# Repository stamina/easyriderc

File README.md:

EasyRider
=========

EasyRider REV C is a motorcycle telemetrics project, developed specifically for my Honda C90 classic bike.

The software is written in C using the libopencm3 library for the STM32 446RE Arm Cortex M4 microcontroller.

The PCB's were created with Kicad 6, you'll find all gerbers/schematics/datasheets in the /docs directory.

Functionality
-------------

EasyRider basically does the following things:

- Controls the lighting system: indicators, rear light, brake light, etc.
- Controls the claxon
- Contains an alarm system, based on an IMU
- Reads the motorcycle battery voltage and the power draw of the board
- Contains a buzzer for some startup/alarm sounds
- Reads the RPM of the motor via the CDI, through an opamp and optocoupled circuit
- Logs GPS coordinates and timestamps of events via the external RTC
- Sends all telemetry data over Bluetooth and writes it to onboard Flash.

Overall changes/benefits compared to Rev B
------------------------------------------

- Way more powerful -> Main board: STM32 Nucleo ARM Cortex 4 32bit mcu with Floating Point Unit
- Way easier debugging with SWD (Serial Wire Debug)
- Smaller form-factor size and more modular -> 2 detachable shields -> riser/daughter boards:
  3x stack of 70mmx80mm boards, connected with double 2x19pin headers (76 pins total)
- EasyRelay board: PSU/Relay grid with connectors and 2x 16 port I/O expander IC's
- EasyComm boards: GPS/Bluetooth/IMU/Flash Storage/Sound(buzzer)
   - Adafruit Ultimate GPS Breakout - 66 channel w/10 Hz updates - Version 3
   - Adafruit LSM6DS33 + LIS3MDL - 9 DoF IMU with Accel / Gyro / Mag - STEMMA QT Qwiic
   - Adafruit Bluefruit LE SPI Friend - Bluetooth Low Energy (BLE)
- 4-layer board instead of 2-layer -> less noise, crosstalk
- Lower power -> most IC's at 3.3V, relay coils at 5V
- Lower power -> switching 5V Voltage Regulator instead of Linear
- Radio connectivity: Bluetooth LE low power instead of power-hungry Wifi
- Fast storage for logging/settings/unique ID's/reboots etc. -> 256MBit WinBond SPI flash memory.
- New smaller molex connectors (Mini-Lock)
- More decoupling cap pads at longer traces
- Seperate 12V higher current wire for claxon relay
- Shift registers/IO expander IC before relays/darlington transitor arrays -> less pins needed on Cortex
- Shift registers/IO expander IC before input sense signals -> less pins needed on Cortex

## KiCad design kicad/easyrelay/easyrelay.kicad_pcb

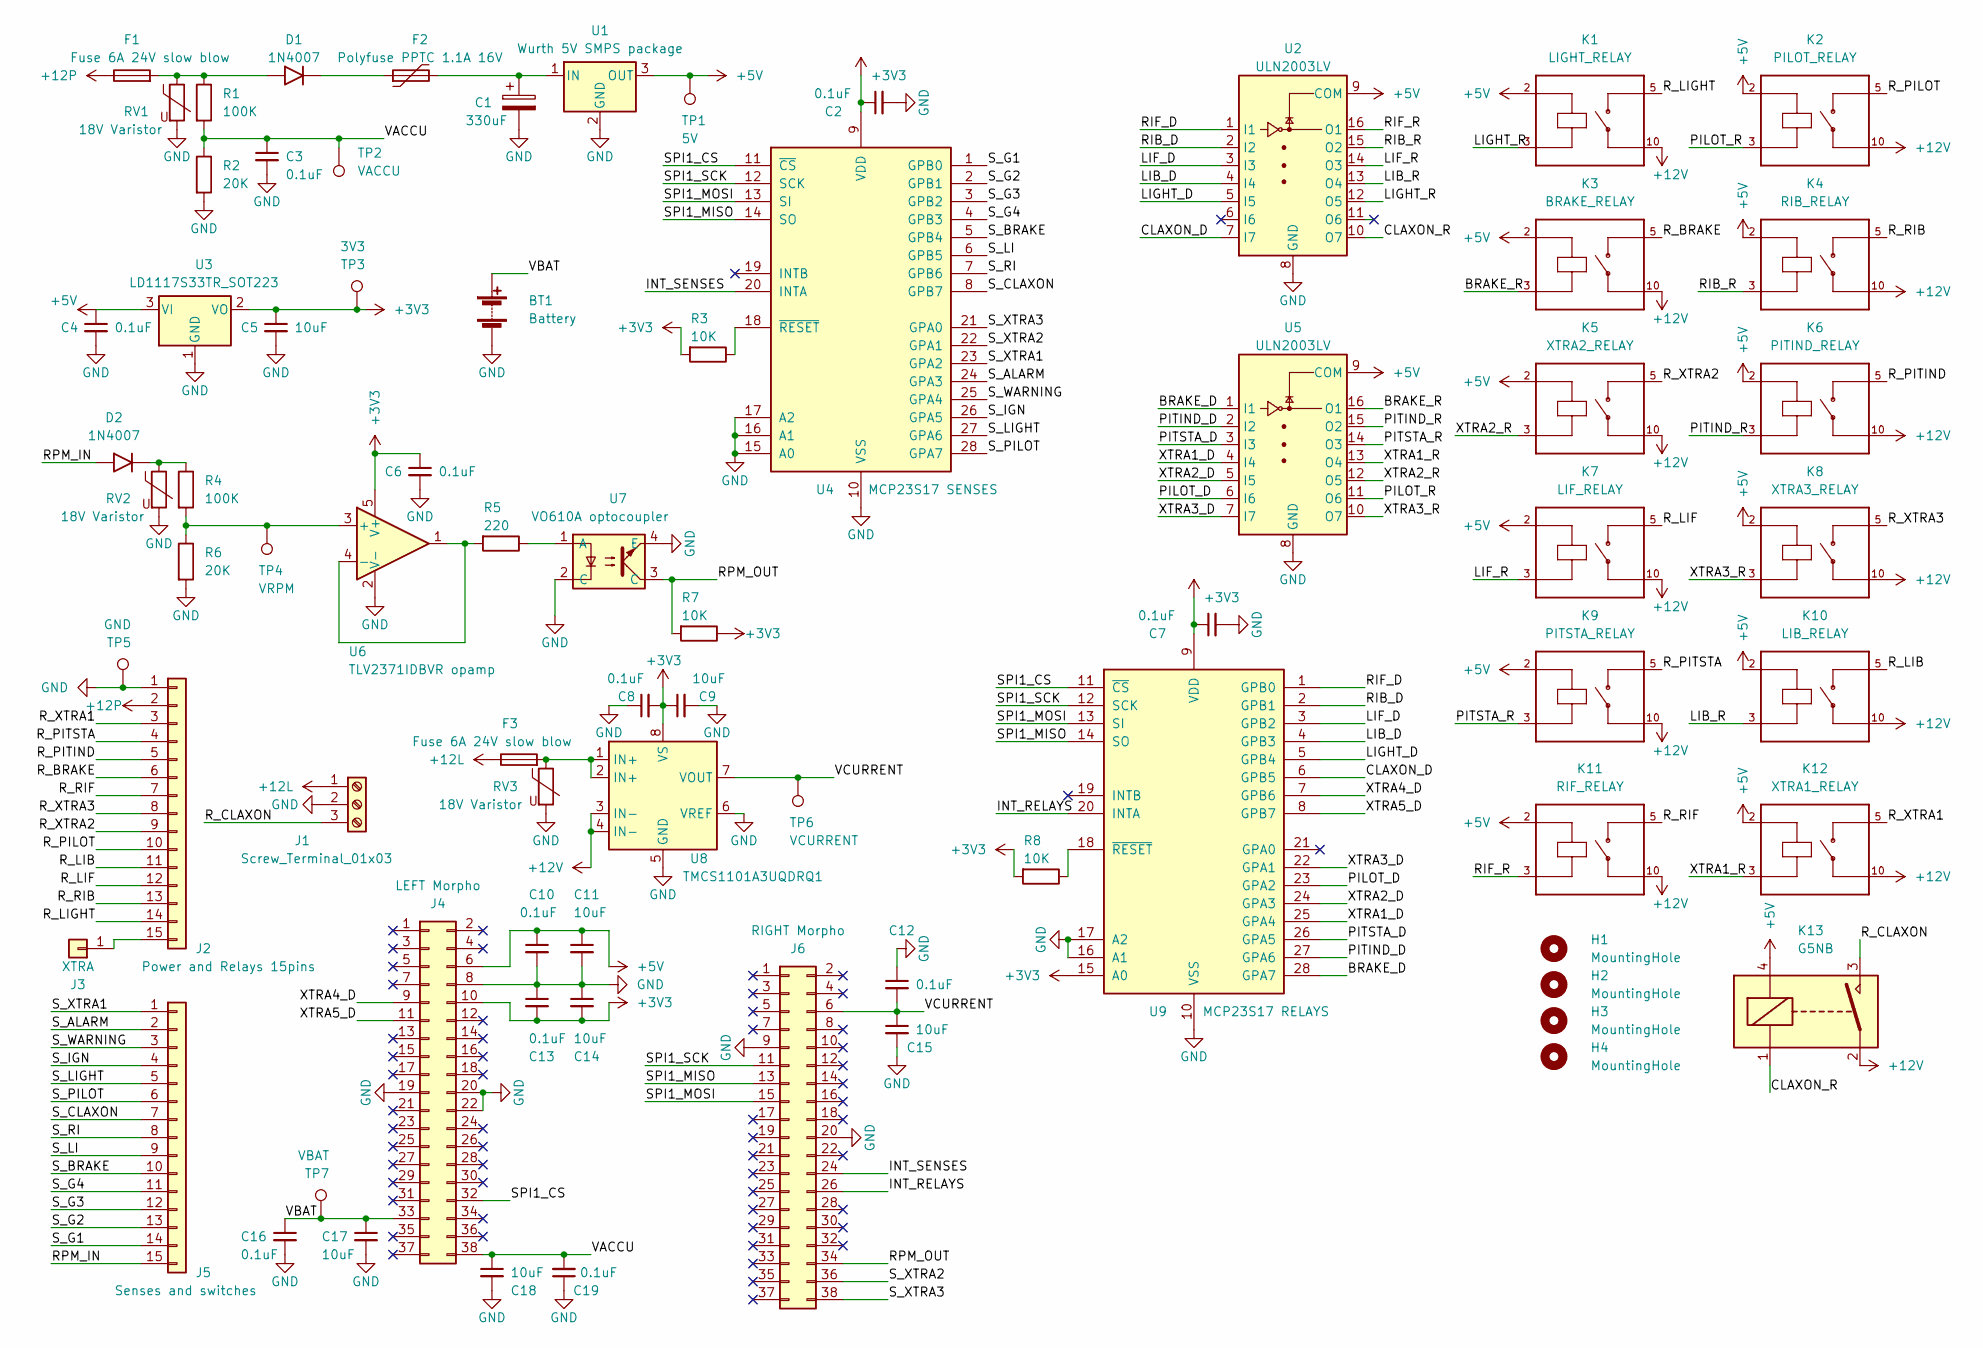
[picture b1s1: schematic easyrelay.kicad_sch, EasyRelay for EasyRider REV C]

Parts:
BT1: Battery; BatteryHolder_Renata SMTU1225-LF
C1: 330uF; CP_Radial_D10.0mm_P5.00mm
C2, C3, C4, C6, C7, C8, C10, C12, C13, C16, C19: 0.1uF; C_0603_1608Metric_Pad1.08x0.95mm_HandSolder
C5, C9, C11, C14, C15, C17, C18: 10uF; C_0603_1608Metric_Pad1.08x0.95mm_HandSolder
D1, D2: 1N4007; D_DO-15_P12.70mm_Horizontal
F1, F3: Fuse 6A 24V slow blow; Fuse_1206_3216Metric
F2: Polyfuse PPTC 1.1A 16V; Fuse_1206_3216Metric
H1, H2, H3, H4: MountingHole; MountingHole_3.2mm_M3
J1: Screw_Terminal_01x03; ScrewTerminalBlock_3_P5.08mm
J2: Power and Relays 15pins; MolexMiniLock_1Ampere_1x15_P2.50mm
J3: XTRA; PinHeader_1x01_P2.54mm_Vertical
J4: LEFT Morpho; PinHeader_2x19_P2.54mm_Vertical
J5: Senses and switches; MolexMiniLock_1Ampere_1x15_P2.50mm
J6: RIGHT Morpho; PinHeader_2x19_P2.54mm_Vertical
K1: LIGHT_RELAY; MEDER RELAY_CRR05-1A
K2: PILOT_RELAY; MEDER RELAY_CRR05-1A
K3: BRAKE_RELAY; MEDER RELAY_CRR05-1A
K4: RIB_RELAY; MEDER RELAY_CRR05-1A
K5: XTRA2_RELAY; MEDER RELAY_CRR05-1A
K6: PITIND_RELAY; MEDER RELAY_CRR05-1A
K7: LIF_RELAY; MEDER RELAY_CRR05-1A
K8: XTRA3_RELAY; MEDER RELAY_CRR05-1A
K9: PITSTA_RELAY; MEDER RELAY_CRR05-1A
K10: LIB_RELAY; MEDER RELAY_CRR05-1A
K11: RIF_RELAY; MEDER RELAY_CRR05-1A
K12: XTRA1_RELAY; MEDER RELAY_CRR05-1A
K13: G5NB; Relay_SPST_Omron-G5NB-1A 5V coil, 12V switch 3Ampere
R1, R4: 100K; R_0603_1608Metric_Pad0.98x0.95mm_HandSolder
R2, R6: 20K; R_0603_1608Metric_Pad0.98x0.95mm_HandSolder
R3, R7, R8: 10K; R_0603_1608Metric_Pad0.98x0.95mm_HandSolder
R5: 220; R_0603_1608Metric_Pad0.98x0.95mm_HandSolder
RV1, RV2, RV3: 18V Varistor; R_0603_1608Metric_Pad0.98x0.95mm_HandSolder
TP1: 5V; PinHeader_1x01_P2.54mm_Vertical
TP2: VACCU; PinHeader_1x01_P2.54mm_Vertical
TP3: 3V3; PinHeader_1x01_P2.54mm_Vertical
TP4: VRPM; PinHeader_1x01_P2.54mm_Vertical
TP5: GND; PinHeader_1x01_P2.54mm_Vertical
TP6: VCURRENT; PinHeader_1x01_P2.54mm_Vertical
TP7: VBAT; PinHeader_1x01_P2.54mm_Vertical
U1: Wurth 5V SMPS package; WURTH-3PIN_FSDM_PACKAGE_TO-220-3_compatible
U2, U5: ULN2003LV; TSSOP16_ULN2003LV
U3: LD1117S33TR_SOT223; SOT-223-3_TabPin2
U4: MCP23S17 SENSES; SSOP-28_5.3x10.2mm_P0.65mm
U6: TLV2371IDBVR opamp; SOT-23-5_HandSoldering
U7: VO610A optocoupler; SMDIP-4_W9.53mm
U8: TMCS1101A3UQDRQ1; SOIC-8_3.9x4.9mm_P1.27mm
U9: MCP23S17 RELAYS; SSOP-28_5.3x10.2mm_P0.65mm

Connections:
+3V3: C2.1, C5.1, C6.1, C7.1, C8.2, C9.1, C13.2, C14.2, J4.10, R3.2, R7.1, R8.2, TP3.1, U3.2 (VO), U4.9 (VDD), U6.5 (V+), U8.8 (VS), U9.9 (VDD), U9.15 (A0); also elsewhere on the board
+5V: C4.1, C10.1, C11.1, J4.6, K1.2, K2.2, K3.2, K4.2, K5.2, K6.2, K7.2, K8.2, K9.2, K10.2, K11.2, K12.2, K13.4, TP1.1, U1.3 (OUT), U2.9 (COM), U3.3 (VI), U5.9 (COM); also elsewhere on the board
+12L: F3.1, J1.1
+12P: F1.1, J2.2
+12V: K1.10, K2.10, K3.10, K4.10, K5.10, K6.10, K7.10, K8.10, K9.10, K10.10, K11.10, K12.10, K13.2, U8.3 (IN-), U8.4 (IN-)
/BRAKE_D: U5.1 (I1), U9.28 (GPA7)
/BRAKE_R: K3.3, U5.16 (O1)
/CLAXON_D: U2.7 (I7), U9.6 (GPB5)
/CLAXON_R: K13.1, U2.10 (O7)
/INT_RELAYS: J6.26, U9.20 (INTA)
/INT_SENSES: J6.24, U4.20 (INTA)
/LIB_D: U2.4 (I4), U9.4 (GPB3)
/LIB_R: K10.3, U2.13 (O4)
/LIF_D: U2.3 (I3), U9.3 (GPB2)
/LIF_R: K7.3, U2.14 (O3)
/LIGHT_D: U2.5 (I5), U9.5 (GPB4)
/LIGHT_R: K1.3, U2.12 (O5)
/PILOT_D: U5.6 (I6), U9.23 (GPA2)
/PILOT_R: K2.3, U5.11 (O6)
/PITIND_D: U5.2 (I2), U9.27 (GPA6)
/PITIND_R: K6.3, U5.15 (O2)
/PITSTA_D: U5.3 (I3), U9.26 (GPA5)
/PITSTA_R: K9.3, U5.14 (O3)
/RIB_D: U2.2 (I2), U9.2 (GPB1)
/RIB_R: K4.3, U2.15 (O2)
/RIF_D: U2.1 (I1), U9.1 (GPB0)
/RIF_R: K11.3, U2.16 (O1)
/RPM_IN: D2.2 (A), J5.15
/RPM_OUT: J6.34, R7.2, U7.3 (C)
/R_BRAKE: J2.6, K3.5
/R_CLAXON: J1.3, K13.3
/R_LIB: J2.11, K10.5
/R_LIF: J2.12, K7.5
/R_LIGHT: J2.14, K1.5
/R_PILOT: J2.10, K2.5
/R_PITIND: J2.5, K6.5
/R_PITSTA: J2.4, K9.5
/R_RIB: J2.13, K4.5
/R_RIF: J2.7, K11.5
/R_XTRA1: J2.3, K12.5
/R_XTRA2: J2.9, K5.5
/R_XTRA3: J2.8, K8.5
/SPI1_CS: J4.32, U4.11 (~CS), U9.11 (~CS)
/SPI1_MISO: J6.13, U4.14 (SO), U9.14 (SO)
/SPI1_MOSI: J6.15, U4.13 (SI), U9.13 (SI)
/SPI1_SCK: J6.11, U4.12 (SCK), U9.12 (SCK)
/S_ALARM: J5.2, U4.24 (GPA3)
/S_BRAKE: J5.10, U4.5 (GPB4)
/S_CLAXON: J5.7, U4.8 (GPB7)
/S_G1: J5.14, U4.1 (GPB0)
/S_G2: J5.13, U4.2 (GPB1)
/S_G3: J5.12, U4.3 (GPB2)
/S_G4: J5.11, U4.4 (GPB3)
/S_IGN: J5.4, U4.26 (GPA5)
/S_LI: J5.9, U4.6 (GPB5)
/S_LIGHT: J5.5, U4.27 (GPA6)
/S_PILOT: J5.6, U4.28 (GPA7)
/S_RI: J5.8, U4.7 (GPB6)
/S_WARNING: J5.3, U4.25 (GPA4)
/S_XTRA1: J5.1, U4.23 (GPA2)
/S_XTRA2: J6.36, U4.22 (GPA1)
/S_XTRA3: J6.38, U4.21 (GPA0)
/VACCU: C3.1, C18.1, C19.2, J4.38, R1.2, R2.1, TP2.1; also elsewhere on the board
/VBAT: BT1.1 (+), C16.1, C17.1, J4.33, TP7.1; also elsewhere on the board
/VCURRENT: C12.2, C15.1, J6.6, TP6.1, U8.7 (VOUT); also elsewhere on the board
/XTRA1_D: U5.4 (I4), U9.25 (GPA4)
/XTRA1_R: K12.3, U5.13 (O4)
/XTRA2_D: U5.5 (I5), U9.24 (GPA3)
/XTRA2_R: K5.3, U5.12 (O5)
/XTRA3_D: U5.7 (I7), U9.22 (GPA1)
/XTRA3_R: K8.3, U5.10 (O7)
/XTRA4_D: J4.9, U9.7 (GPB6)
/XTRA5_D: J4.11, U9.8 (GPB7)
GND: BT1.2 (-), C1.2, C2.2, C3.2, C4.2, C5.2, C6.2, C7.2, C8.1, C9.2, C10.2, C11.2, C12.1, C13.1, C14.1, C15.2, C16.2, C17.2, C18.2, C19.1, J1.2, J2.1, J4.8, J4.19, J4.20, J4.22, J6.9, J6.20, R2.2, R6.2, RV1.2, RV2.2, RV3.2, TP5.1, U1.2 (GND), U2.8 (GND), U3.1 (GND), U4.10 (VSS), U4.15 (A0), U4.16 (A1), U4.17 (A2), U5.8 (GND), U6.2 (V-), U7.2 (C), U7.4 (E), U8.5 (GND), U8.6 (VREF), U9.10 (VSS), U9.16 (A1), U9.17 (A2); also elsewhere on the board
unnamed: C1.1, F2.2, U1.1 (IN)
unnamed: D1.1 (K), F2.1
unnamed: D1.2 (A), F1.2, R1.1, RV1.1
unnamed: D2.1 (K), R4.1, RV2.1
unnamed: F3.2, RV3.1, U8.1 (IN+), U8.2 (IN+)
unnamed: J2.15, J3.1
unnamed: R3.1, U4.18 (~RESET)
unnamed 81: R4.2, R6.1, TP4.1, U6.3 (+); also elsewhere on the board
unnamed: R5.1, U7.1 (A)
unnamed: R5.2, U6.1, U6.4 (-)
unnamed: R8.1, U9.18 (~RESET)

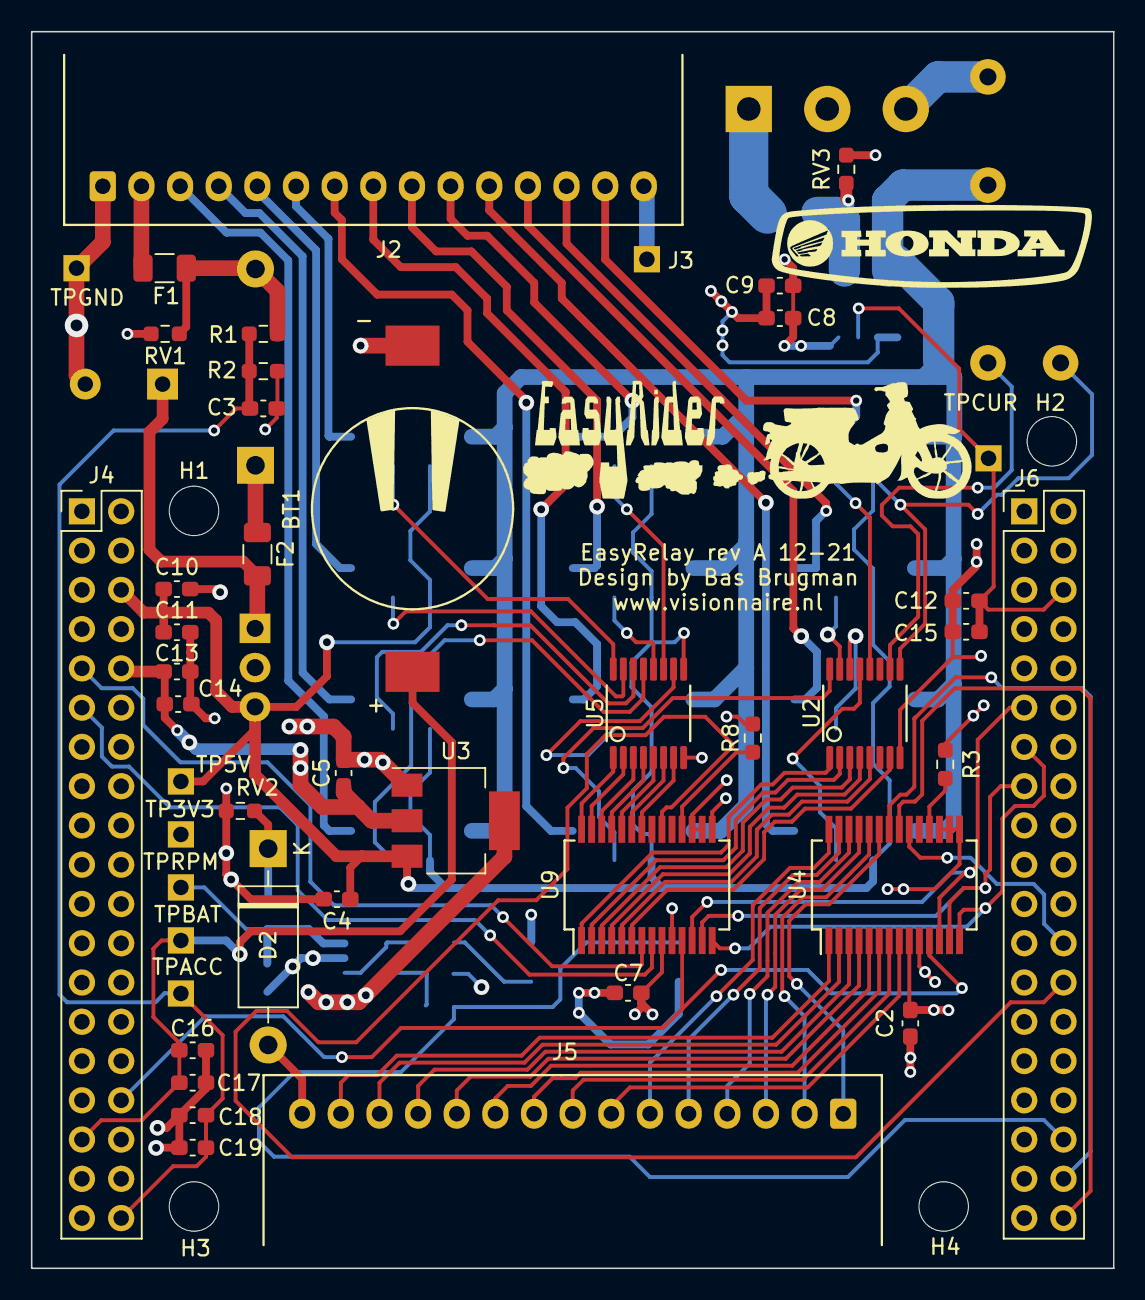
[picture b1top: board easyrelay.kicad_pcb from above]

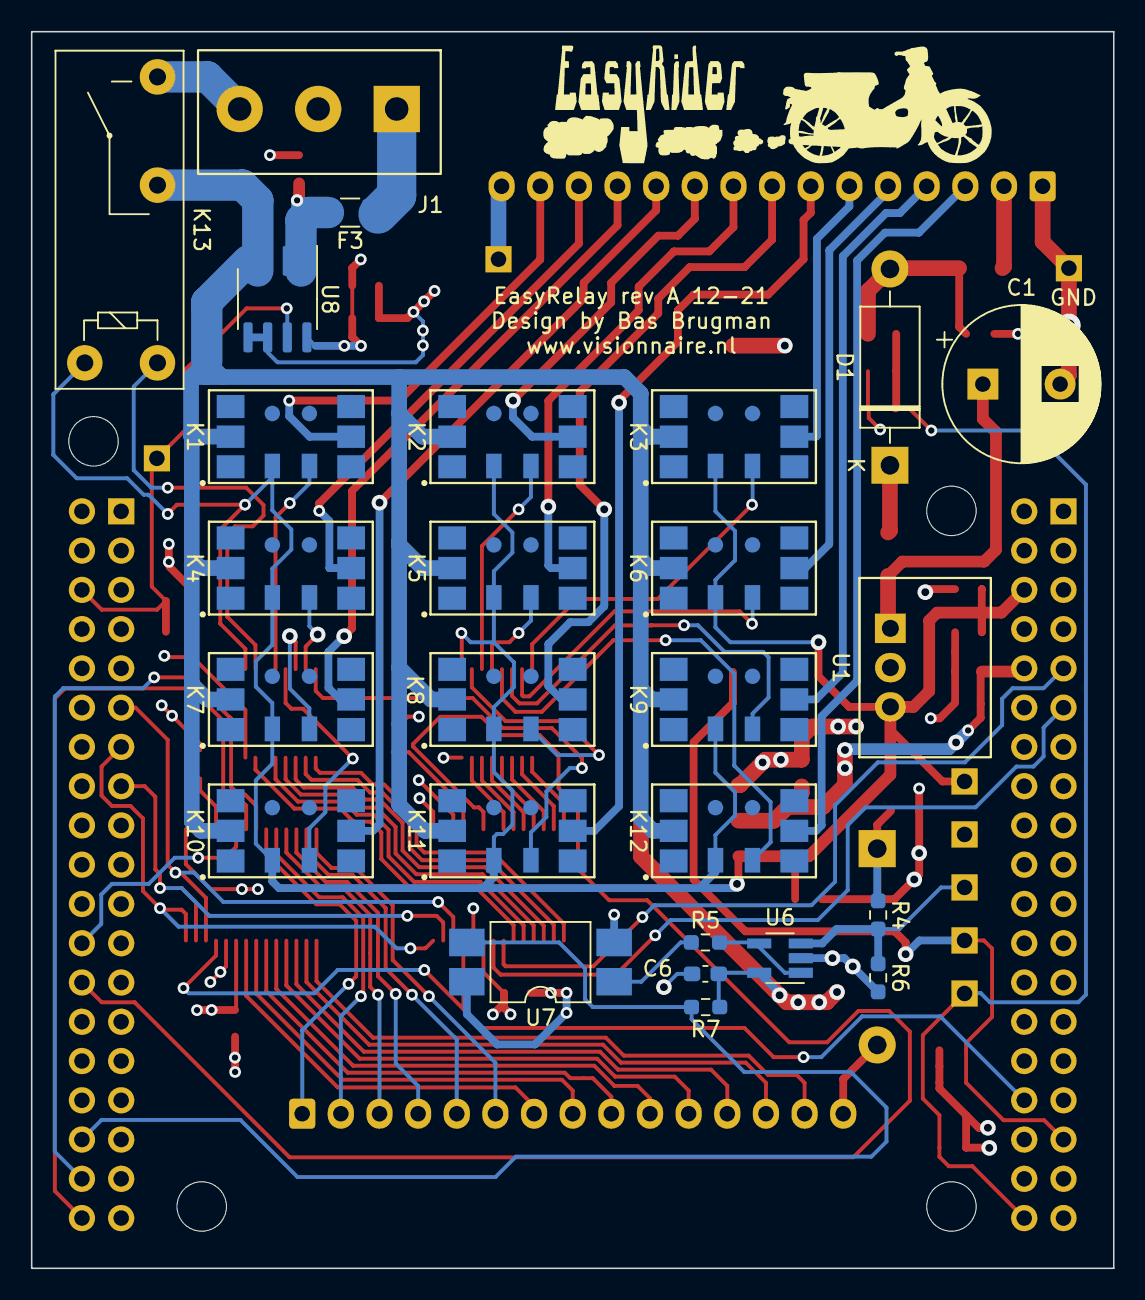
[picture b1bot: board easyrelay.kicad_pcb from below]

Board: 4 copper layers, 70.0 x 80.0 mm, 75 parts (27 on the bottom side), 85 nets.

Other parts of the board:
TP3V3: 3V3; PinHeader_1x01_P2.54mm_Vertical
TP5V: 5V; PinHeader_1x01_P2.54mm_Vertical
TPACC: VACCU; PinHeader_1x01_P2.54mm_Vertical
TPBAT: VBAT; PinHeader_1x01_P2.54mm_Vertical
TPCUR: VCURRENT; PinHeader_1x01_P2.54mm_Vertical
TPGND: GND; PinHeader_1x01_P2.54mm_Vertical
TPRPM: VRPM; PinHeader_1x01_P2.54mm_Vertical

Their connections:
+3V3: TP3V3.1; also elsewhere on the board
+5V: TP5V.1; also elsewhere on the board
/VACCU: TPACC.1; also elsewhere on the board
/VBAT: TPBAT.1; also elsewhere on the board
/VCURRENT: TPCUR.1; also elsewhere on the board
GND: TPGND.1; also elsewhere on the board
unnamed 81: TPRPM.1; also elsewhere on the board

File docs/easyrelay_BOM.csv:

"Id";"Designator";"Package";"Quantity";"Designation";"Supplier and ref";
1;"U2,U5";"TSSOP16_ULN2003LV";2;"ULN2003LV";;;
2;"H4,H3,H2,H1";"MountingHole_3.2mm_M3";4;"MountingHole";;;
3;"J4";"PinHeader_2x19_P2.54mm_Vertical";1;"LEFT Morpho";;;
4;"BT1";"BatteryHolder_Renata SMTU1225-LF";1;"Battery";;;
5;"R2,R6";"R_0603_1608Metric_Pad0.98x0.95mm_HandSolder";2;"20K";;;
6;"C18,C5,C14,C15,C17,C9,C11";"C_0603_1608Metric_Pad1.08x0.95mm_HandSolder";7;"10uF";;;
7;"R8,R3,R7";"R_0603_1608Metric_Pad0.98x0.95mm_HandSolder";3;"10K";;;
8;"C4,C2,C13,C10,C12,C16,C8,C3,C19,C7,C6";"C_0603_1608Metric_Pad1.08x0.95mm_HandSolder";11;"0.1uF";;;
9;"TP5V";"PinHeader_1x01_P2.54mm_Vertical";1;"5V";;;
10;"U9";"SSOP-28_5.3x10.2mm_P0.65mm";1;"MCP23S17 RELAYS";;;
11;"TPCUR";"PinHeader_1x01_P2.54mm_Vertical";1;"VCURRENT";;;
12;"RV2,RV1,RV3";"R_0603_1608Metric_Pad0.98x0.95mm_HandSolder";3;"18V Varistor";;;
13;"U3";"SOT-223-3_TabPin2";1;"LD1117S33TR_SOT223";;;
14;"D2,D1";"D_DO-15_P12.70mm_Horizontal";2;"1N4007";;;
15;"J5";"MolexMiniLock_1Ampere_1x15_P2.50mm";1;"Senses and switches";;;
16;"F1,F3";"Fuse_1206_3216Metric";2;"Fuse 6A 24V slow blow";;;
17;"R1,R4";"R_0603_1608Metric_Pad0.98x0.95mm_HandSolder";2;"100K";;;
18;"TP3V3";"PinHeader_1x01_P2.54mm_Vertical";1;"3V3";;;
19;"TPRPM";"PinHeader_1x01_P2.54mm_Vertical";1;"VRPM";;;
20;"J3";"PinHeader_1x01_P2.54mm_Vertical";1;"XTRA";;;
21;"J6";"PinHeader_2x19_P2.54mm_Vertical";1;"RIGHT Morpho";;;
22;"TPBAT";"PinHeader_1x01_P2.54mm_Vertical";1;"VBAT";;;
23;"U4";"SSOP-28_5.3x10.2mm_P0.65mm";1;"MCP23S17 SENSES";;;
24;"G***,G***";"EasyRider_logo1";2;"LOGO";;;
25;"J2";"MolexMiniLock_1Ampere_1x15_P2.50mm";1;"Power and Relays 15pins";;;
26;"TPACC";"PinHeader_1x01_P2.54mm_Vertical";1;"VACCU";;;
27;"F2";"Fuse_1206_3216Metric";1;"Polyfuse PPTC 1.1A 16V";;;
28;"G***";"EasyRider_logo2";1;"LOGO";;;
29;"K1";"MEDER RELAY_CRR05-1A";1;"LIGHT_RELAY";;;
30;"U7";"SMDIP-4_W9.53mm";1;"VO610A optocoupler";;;
31;"K11";"MEDER RELAY_CRR05-1A";1;"RIF_RELAY";;;
32;"K4";"MEDER RELAY_CRR05-1A";1;"RIB_RELAY";;;
33;"K6";"MEDER RELAY_CRR05-1A";1;"PITIND_RELAY";;;
34;"U8";"SOIC-8_3.9x4.9mm_P1.27mm";1;"TMCS1101A3UQDRQ1";;;
35;"J1";"ScrewTerminalBlock_3_P5.08mm";1;"Screw_Terminal_01x03";;;
36;"K8";"MEDER RELAY_CRR05-1A";1;"XTRA3_RELAY";;;
37;"K9";"MEDER RELAY_CRR05-1A";1;"PITSTA_RELAY";;;
38;"K2";"MEDER RELAY_CRR05-1A";1;"PILOT_RELAY";;;
39;"K12";"MEDER RELAY_CRR05-1A";1;"XTRA1_RELAY";;;
40;"K10";"MEDER RELAY_CRR05-1A";1;"LIB_RELAY";;;
41;"K13";"Relay_SPST_Omron-G5NB-1A 5V coil, 12V switch 3Ampere";1;"G5NB";;;
42;"C1";"CP_Radial_D10.0mm_P5.00mm";1;"330uF";;;
43;"K3";"MEDER RELAY_CRR05-1A";1;"BRAKE_RELAY";;;
44;"U1";"WURTH-3PIN_FSDM_PACKAGE_TO-220-3_compatible";1;"Wurth 5V SMPS package";;;
45;"K5";"MEDER RELAY_CRR05-1A";1;"XTRA2_RELAY";;;
46;"TPGND";"PinHeader_1x01_P2.54mm_Vertical";1;"GND";;;
47;"R5";"R_0603_1608Metric_Pad0.98x0.95mm_HandSolder";1;"220";;;
48;"K7";"MEDER RELAY_CRR05-1A";1;"LIF_RELAY";;;
49;"U6";"SOT-23-5_HandSoldering";1;"TLV2371IDBVR opamp";;;

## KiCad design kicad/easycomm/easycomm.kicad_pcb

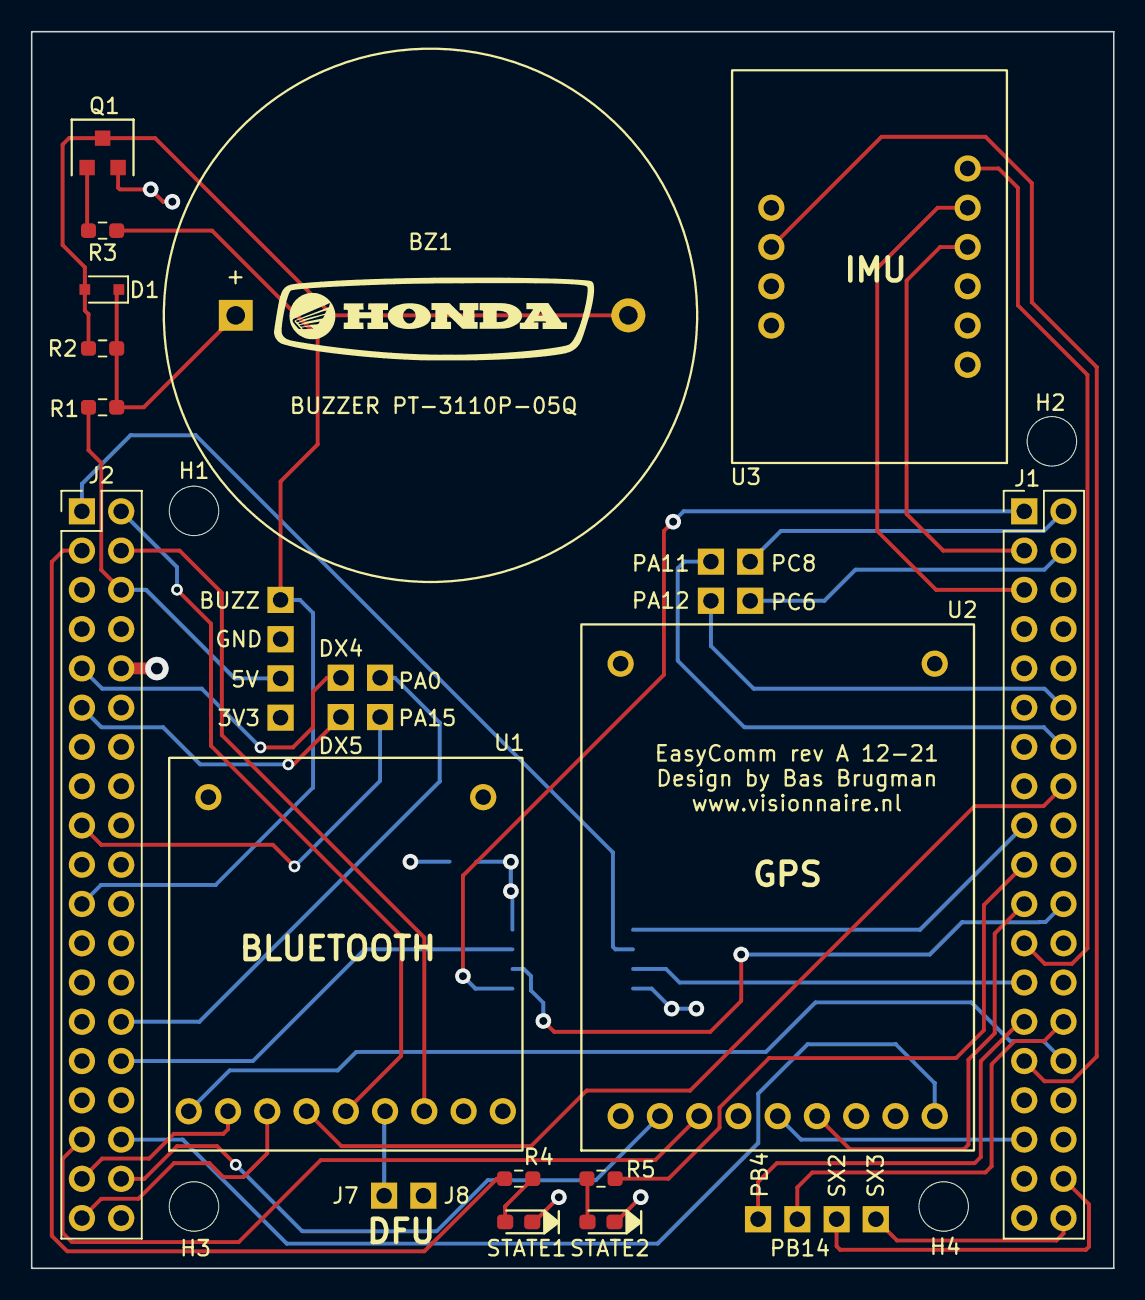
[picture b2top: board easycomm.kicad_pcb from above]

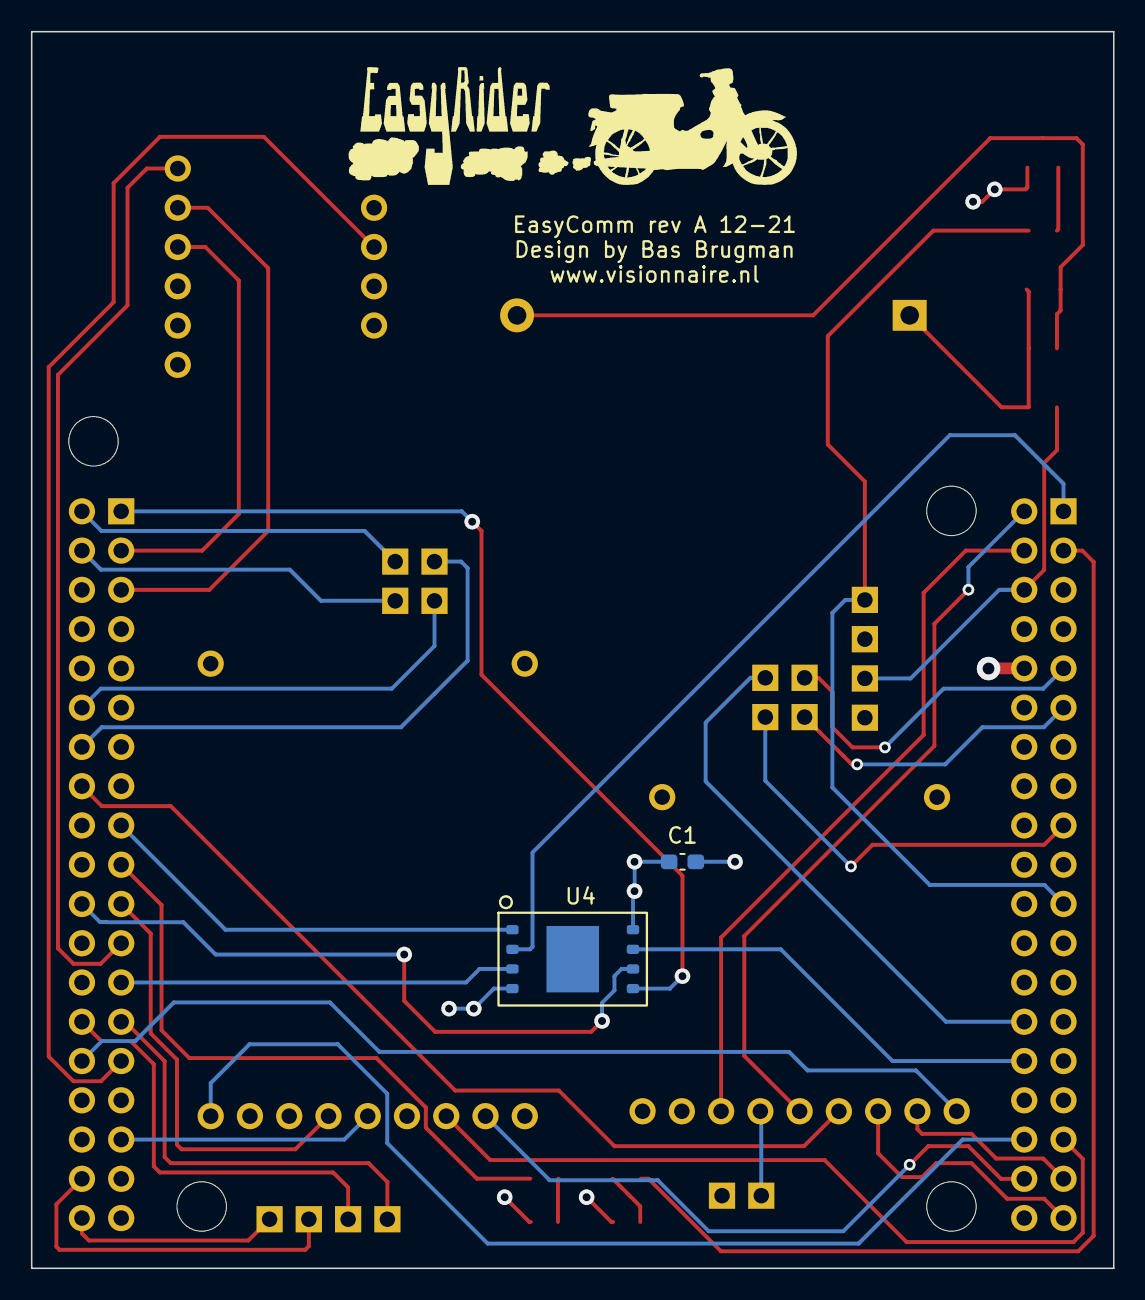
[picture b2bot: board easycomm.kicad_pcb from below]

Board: 4 copper layers, 70.0 x 80.0 mm, 39 parts (2 on the bottom side), 45 nets.

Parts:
3V3, 5V: TestPoint; PinHeader_1x01_P2.54mm_Vertical
BUZZ: TestPoint; PinHeader_1x01_P2.54mm_Vertical
BZ1: Buzzer; Buzzer_25.4mmPP
C1: 0.1uf; C_0603_1608Metric_Pad1.08x0.95mm_HandSolder
D1: D_Schottky; D_SOD-323F
DX4, DX5: Conn_01x01; PinHeader_1x01_P2.54mm_Vertical
GND: TestPoint; PinHeader_1x01_P2.54mm_Vertical
H1, H2, H3, H4: MountingHole; MountingHole_3.2mm_M3
J1: RIGHT Morpho; PinHeader_2x19_P2.54mm_Vertical
J2: LEFT Morpho; PinHeader_2x19_P2.54mm_Vertical
J7, J8: Conn_01x01; PinHeader_1x01_P2.54mm_Vertical
PA0, PA11, PA12, PA15: Conn_01x01; PinHeader_1x01_P2.54mm_Vertical
PB4, PB14: Conn_01x01; PinHeader_1x01_P2.54mm_Vertical
PC6, PC8: Conn_01x01; PinHeader_1x01_P2.54mm_Vertical
Q1: NPN2222A; SOT-23_3_HandSoldering
R1: 2.7K; R_0603_1608Metric_Pad0.98x0.95mm_HandSolder
R2: 1K; R_0603_1608Metric_Pad0.98x0.95mm_HandSolder
R3, R4, R5: 330; R_0603_1608Metric_Pad0.98x0.95mm_HandSolder
STATE1, STATE2: LED; LED_0603_1608Metric_Pad1.05x0.95mm_HandSolder
SX2, SX3: Conn_01x01; PinHeader_1x01_P2.54mm_Vertical
U1: Adafruit_Bluetooth
U2: Adafruit_GPS
U3: Adafruit_IMU
U4: W25Q256JV; WSON-8-8x6mm_P1.27mm

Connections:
+3V3: 3V3.1, C1.1, J2.10, U1.9 (VIN), U2.8 (VIN), U3.1 (Vin), U4.8 (VCC)
+5V: 5V.1, J2.6, R1.1
/BLE_CLK: J1.30, U1.1 (CLK)
/BLE_CS: J1.16, U1.4 (CS)
/BLE_IRQ: J2.2, U1.5 (IRQ)
/BLE_MISO: J2.35, U1.2 (MISO)
/BLE_MOSI: J2.37, U1.3 (MOSI)
/BLE_RST: J2.4, U1.7 (RST)
/BUZZ: BUZZ.1, J2.21, R3.2
/DFU: J7.1, U1.6 (DFU)
/FLASH_CLK: J1.22, U4.6 (CLK)
/FLASH_CS: J1.17, U4.1 (~CS)
/FLASH_IO0: J1.1, U4.5 (DI(IO0))
/FLASH_IO1: J2.1, U4.2 (DO(IO1))
/FLASH_RESET: J2.30, U4.7 (IO3/HOLD/RESET)
/FLASH_WP: J1.25, U4.3 (IO2/WP)
/GPS_ENABLE: J2.36, U2.2 (ENABLE)
/IMU_INT1: J1.29, U3.9 (INT1)
/IMU_SCL: J1.3, U3.4 (SCL)
/IMU_SDA: J1.5, U3.5 (SDA)
/INTM: J1.23, U3.6 (INTM)
/LED_STATUS1: J2.3, R4.2
/LED_STATUS2: J1.19, R5.2
/PA0: J2.28, PA0.1
/PA11: J1.14, PA11.1
/PA12: J1.12, PA12.1
/PA15: J2.17, PA15.1
/PB4: J1.27, PB4.1
/PB14: J1.28, PB14.1
/PC6: J1.4, PC6.1
/PC8: J1.2, PC8.1
/PPS: J2.34, U2.9 (PPS)
/RX_TX: J1.21, U2.6 (RX)
/S_XTRA2: J1.36, SX2.1
/S_XTRA3: J1.38, SX3.1
/TX_RX: J1.33, U2.5 (TX)
/VBAT: J2.33, U2.3 (VBAT)
/XTRA4_D: DX4.1, J2.9
/XTRA5_D: DX5.1, J2.11
GND: C1.2, GND.1, J1.9, J1.20, J2.8, J2.19, J2.20, J2.22, J8.1, Q1.2 (E), STATE1.1 (K), STATE2.1 (K), U1.8 (GND), U2.7 (GND), U3.3 (GND), U4.4 (GND)
unnamed: BZ1.1 (-), D1.1 (K), R1.2, R2.1
unnamed: BZ1.2 (+), D1.2 (A), Q1.3 (C), R2.2
unnamed: R4.1, STATE1.2 (A)
unnamed: R5.1, STATE2.2 (A)
unnamed: Q1.1 (B), R3.1

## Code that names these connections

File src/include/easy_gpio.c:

/* Copyright (C) 2021 Bas Brugman
 * http://www.visionnaire.nl
 *
 * This program is free software: you can redistribute it and/or modify
 * it under the terms of the GNU General Public License as published by
 * the Free Software Foundation, either version 3 of the License,
 * or (at your option) any later version.
 *
 * This program is distributed in the hope that it will be useful,
 * but WITHOUT ANY WARRANTY; without even the implied warranty of
 * MERCHANTABILITY or FITNESS FOR A PARTICULAR PURPOSE.  See the
 * GNU General Public License for more details.
 *
 * You should have received a copy of the GNU General Public License
 * along with this program.  If not, see <https://www.gnu.org/licenses/>.
 *
 */
#include "easy_gpio.h"

#include "easy_buzz.h"
#include "easy_clock.h"
#include "easy_debug.h"
#include "easy_spi.h"
#include "easy_state.h"
#include "stdio.h"

// portA
#define S_XTRA3 1  // future use
#define S_XTRA2 2  // future use
#define S_XTRA1 4  // used to calibrate/zero out IMU values
#define S_ALARM 8
#define S_WARNING 16
#define S_IGNITION 32
#define S_LIGHT 64
#define S_PILOT 128

// portB
#define S_G1 1
#define S_G2 2
#define S_G3 4
#define S_G4 8
#define S_BRAKE 16
#define S_LI 32
#define S_RI 64
#define S_CLAXON 128

#define SENSE_DEBOUNCE_CHECKS 5
#define RELAYS_DEBOUNCE_CHECKS 5

uint8_t g_senses_checks;
uint8_t g_relays_checks;
uint8_t g_senses_debounce_pending;
uint8_t g_relays_debounce_pending;
uint8_t g_cur_sense_gpio_a;
uint8_t g_cur_sense_gpio_b;

// proto's
void dispatch_senses(void);
void check_neutral(void);

void gpio_setup() {
  rcc_periph_clock_enable(RCC_GPIOA);
  rcc_periph_clock_enable(RCC_GPIOB);
  rcc_periph_clock_enable(RCC_GPIOC);
  // status leds
  gpio_mode_setup(GPIOC, GPIO_MODE_OUTPUT, GPIO_PUPD_NONE, GPIO7);
  gpio_mode_setup(GPIOC, GPIO_MODE_OUTPUT, GPIO_PUPD_NONE, GPIO12);
  // interrupt pin SENSES PB1 and interrupt pin RELAYS PB15
  // NOTE: since the RELAYS I/O expander is set only with output pins, we're not
  // using PB15 atm (XTRA4 and XTRA5 are not used and can be configured
  // as inputs later on: future use)
  gpio_mode_setup(GPIOB, GPIO_MODE_INPUT, GPIO_PUPD_NONE, GPIO1 | GPIO15);
}

void dispatch_senses() {
#if EASY_DEBUG
  debug_write("DISPATCH EVENTS\n");
#endif
  // NOTE: S_XTRA1-3 are not used atm, these pins are for future senses
  // pin == 1, means sense is OFF, pin == 0, means sense is ON (pulled down)
  (g_cur_sense_gpio_a & S_ALARM) ? set_event(EV_ALARM_SET_OFF)
                                 : set_event(EV_ALARM_SET_ON);
  (g_cur_sense_gpio_a & S_WARNING) ? set_event(EV_WARNING_OFF)
                                   : set_event(EV_WARNING_ON);
  (g_cur_sense_gpio_a & S_IGNITION) ? set_event(EV_IGN_OFF)
                                    : set_event(EV_IGN_ON);
  (g_cur_sense_gpio_a & S_LIGHT) ? set_event(EV_LIGHT_OFF)
                                 : set_event(EV_LIGHT_ON);
  (g_cur_sense_gpio_a & S_PILOT) ? set_event(EV_PILOT_OFF)
                                 : set_event(EV_PILOT_ON);
  (g_cur_sense_gpio_b & S_G1) ? set_event(EV_GEAR1_OFF)
                              : set_event(EV_GEAR1_ON);
  (g_cur_sense_gpio_b & S_G2) ? set_event(EV_GEAR2_OFF)
                              : set_event(EV_GEAR2_ON);
  (g_cur_sense_gpio_b & S_G3) ? set_event(EV_GEAR3_OFF)
                              : set_event(EV_GEAR3_ON);
  (g_cur_sense_gpio_b & S_G4) ? set_event(EV_GEAR4_OFF)
                              : set_event(EV_GEAR4_ON);
  (g_cur_sense_gpio_b & S_BRAKE) ? set_event(EV_BRAKE_OFF)
                                 : set_event(EV_BRAKE_ON);
  (g_cur_sense_gpio_b & S_LI) ? set_event(EV_LI_OFF) : set_event(EV_LI_ON);
  (g_cur_sense_gpio_b & S_RI) ? set_event(EV_RI_OFF) : set_event(EV_RI_ON);
  (g_cur_sense_gpio_b & S_CLAXON) ? set_event(EV_CLAXON_OFF)
                                  : set_event(EV_CLAXON_ON);
}

void process_senses() {
  // if PB1 == HIGH (incoming sense change interrupt)
  // read both INT capture ports
  // start 5ms timer
  // read both GPIO ports 5 times in a row with 5ms delta's
  // compare them to the INT capture ports
  if (gpio_get(GPIOB, GPIO1)) {
#if EASY_DEBUG
    char buf[255];
    snprintf(buf, 255, "SENSE INT CAPTURE PORT A/B: %d %d\n",
             read_sense_capture_a(), read_sense_capture_b());
    debug_write(buf);
#endif
    g_cur_sense_gpio_a = read_sense_port_a();
    g_cur_sense_gpio_b = read_sense_port_b();
    g_senses_debounce_pending = 1;
    g_senses_checks = SENSE_DEBOUNCE_CHECKS;
  }
  if (g_senses_debounce_pending) {
    if (g_senses_checks) {                        // debouncing checks
      if (!get_1ms_tick_slot(SENSES_1MS_SLOT)) {  // 5ms passed
        // current GPIO not equal anymore -> noise bounce
        // bailout with no senses events dispatched
        // NOTE: this noise bounce would retrigger an interrupt
        // so we automatically restart the checks again
        if ((g_cur_sense_gpio_a != read_sense_port_a()) ||
            (g_cur_sense_gpio_b != read_sense_port_b())) {
          g_senses_debounce_pending = 0;
        } else {
          g_senses_checks--;
          if (g_senses_checks) {
            set_1ms_tick_slot(SENSES_1MS_SLOT, 5);
          }
        }
      }
    } else {  // debouncing checks done, dispatch events
      g_senses_debounce_pending = 0;
      dispatch_senses();
    }
  }
  // check for neutral, which doesn't have its own sense wire, but should be
  // activated when the gear1-4 substates are all off.
  check_neutral();
  // TODO: check_active_settle()
  // check the tick_slot for active_settle and cast a EV_ACTIVE_SETTLE_OFF
}

void check_neutral() {
  if (get_neutral_pending()) {
    if (!get_100ms_tick_slot(NEUTRAL_100MS_SLOT)) {
      // only set neutral, when no other gears are on
      if (!(check_substate(ST_GEAR1) || check_substate(ST_GEAR2) ||
            check_substate(ST_GEAR3) || check_substate(ST_GEAR4))) {
        set_event(EV_NEUTRAL_ON);
      }
      set_neutral_pending(0);
    }
  }
}

void set_status_led1(uint32_t blinkspd) {
  if (blinkspd) {
    ;
    ;
  }
  // slow blink
  if (!get_1s_tick_slot(LED1_1S_SLOT)) {
    gpio_toggle(GPIOC, GPIO12);
    set_1s_tick_slot(LED1_1S_SLOT, 1);
  }
  // fast blink
  /*if (!get_100ms_tick_slot(LED1_100MS_SLOT)) {*/
  /*gpio_toggle(GPIOA, GPIO5);*/
  /*set_100ms_tick_slot(LED1_100MS_SLOT, 1);*/
  /*}*/
}

void set_status_led2(uint32_t blinkspd) {
  if (blinkspd) {
    ;
    ;
  }
  // slow blink
  if (!get_1s_tick_slot(LED2_1S_SLOT)) {
    gpio_toggle(GPIOC, GPIO7);
    set_1s_tick_slot(LED2_1S_SLOT, 1);
  }
}

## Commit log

2022-01-18 Initial commit, Github repo
2022-01-18 Adding KiCAD files
2022-01-28 Added SPI code for MCP23S17 and sense/relay logic
2022-02-10 Basis senses (switch pins) working
2022-02-10 Updating info.txt
